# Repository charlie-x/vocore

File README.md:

# vocore eagle BRD files

Eagle BRD files for the VoCore and the VoCore dock, 7.x Eagle

notes:

	VIAs and drill sizes/restring need to be set for your board house.
	I'm using a temporary 4 layer DRC
	Layers are setup so shouldn't be any blind/buried vias

NOT BUILD TESTED - THERE WILL BE ERRORS!

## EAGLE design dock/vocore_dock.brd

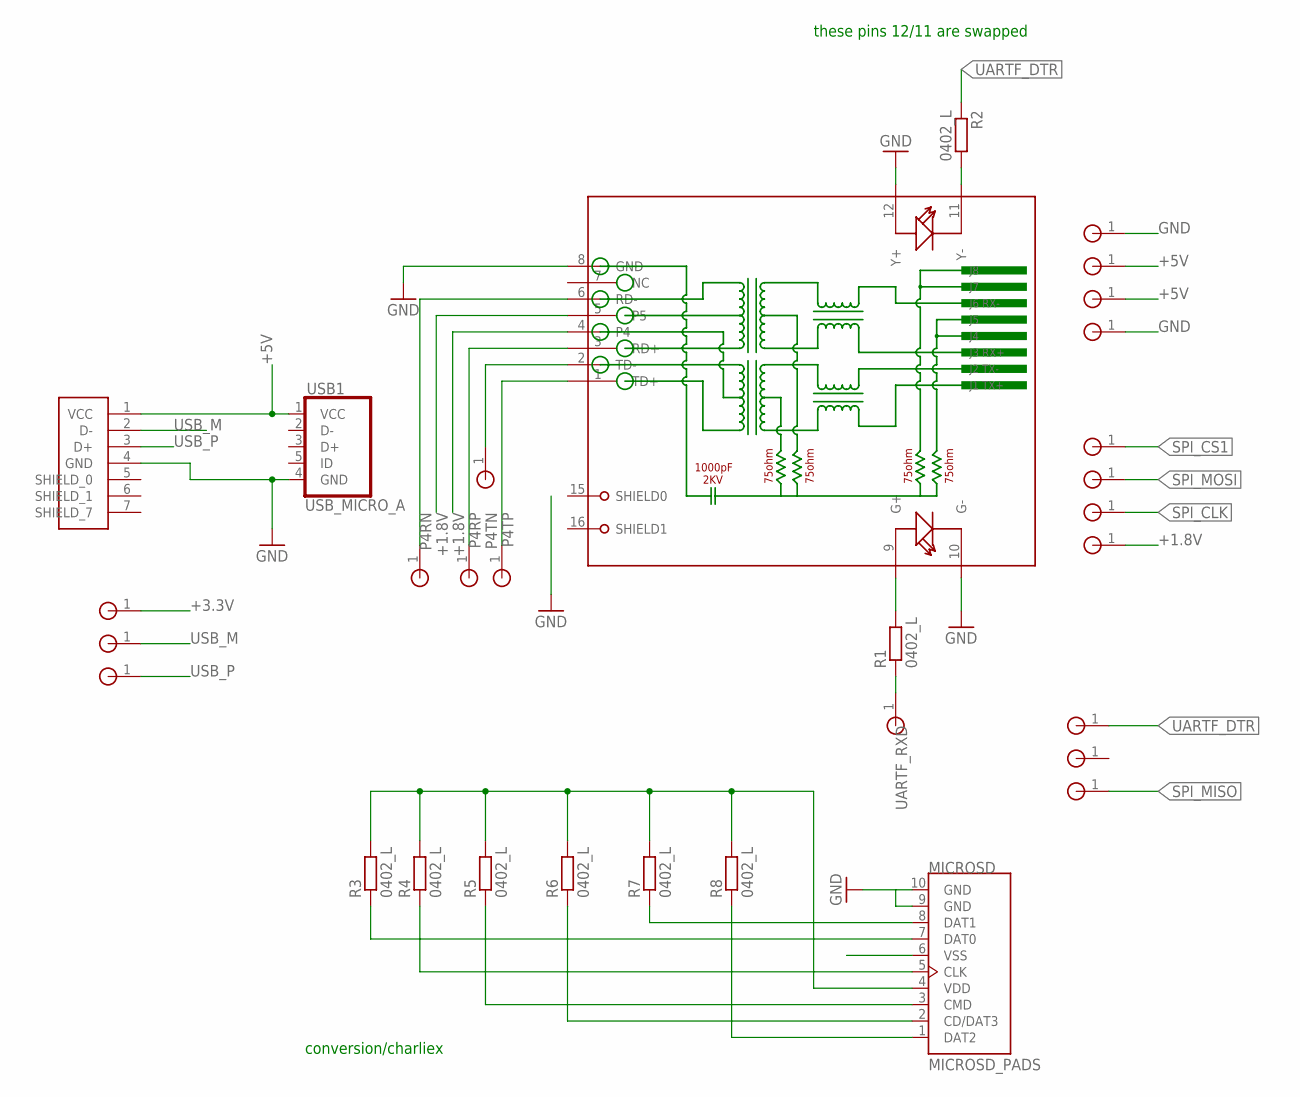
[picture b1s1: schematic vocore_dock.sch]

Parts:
MICROSD: MICROSD_PADS; MICROSD_PADS_1PRIMARY
PB04, PB05, PB06, PB07, PB12, PB13, PB14, PB15, PB16, PB17, PB18: PORT_1PIN; PORT_1PIN_DECAL_1PRIMARY
PL05, PL06, PL07, PL08: PORT_1PIN; PORT_1PIN_DECAL_1PRIMARY
PT01, PT02, PT03, PT04: PORT_1PIN; PORT_1PIN_DECAL_1PRIMARY
R1, R2, R3, R4, R5, R6, R7, R8: 0402_L; 0402_L_1PRIMARY
RJ45: RJ45ALED; RJ45ALED_1PRIMARY
USB1: USB_MICRO_A; USB_MICRO_A_1PRIMARY
USB2: USB_FULL_TALL; USB_FULL_TALL_1PRIMARY

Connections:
+1.8V: PL05.1, RJ45.4, RJ45.5
+3.3V: MICROSD.4 (VDD), PB18.1, R3.2, R4.2, R5.2, R6.2, R7.2, R8.2
+5V: PT02.1, PT03.1, USB1.1 (VCC), USB2.1 (VCC)
GND: MICROSD.6 (VSS), MICROSD.9 (GND), MICROSD.10 (GND), PT01.1, PT04.1, RJ45.8 (GND), RJ45.10 (G-), RJ45.12 (Y+), USB1.4 (GND), USB2.4 (GND)
LED_G: R1.2, RJ45.9 (G+)
LED_Y: R2.2, RJ45.11 (Y-)
P4RN: PB15.1, RJ45.6 (RD-)
P4RP: PB14.1, RJ45.3 (RD+)
P4TN: PB12.1, RJ45.2 (TD-)
P4TP: PB13.1, RJ45.1 (TD+)
SPI_CLK: MICROSD.5 (CLK), PL06.1, R4.1
SPI_CS1: MICROSD.2 (CD/DAT3), PL08.1, R6.1
SPI_MISO: MICROSD.7 (DAT0), PB05.1, R3.1
SPI_MOSI: MICROSD.3 (CMD), PL07.1, R5.1
SPI_RSV1: MICROSD.8 (DAT1), R7.1
SPI_RSV2: MICROSD.1 (DAT2), R8.1
UARTF_DTR: PB07.1, R2.1
UARTF_RXD: PB04.1, R1.1
USB_M: PB16.1, USB2.2 (D-)
USB_P: PB17.1, USB2.3 (D+)

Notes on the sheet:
these pins 12/11 are swapped
conversion/charliex

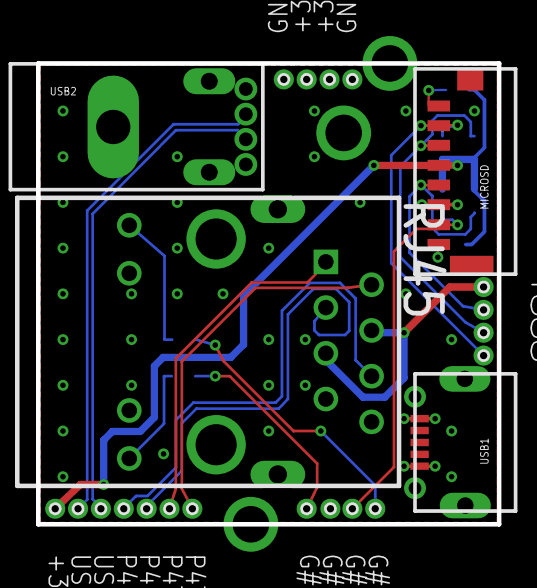
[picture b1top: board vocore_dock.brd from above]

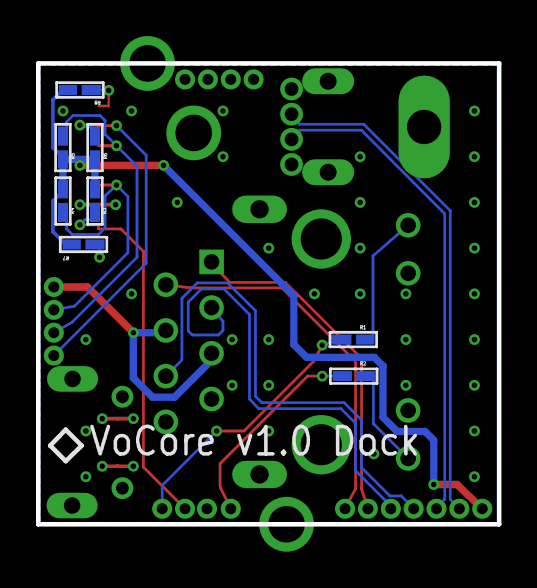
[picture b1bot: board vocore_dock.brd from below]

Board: 4 copper layers, 25.6 x 25.6 mm, 34 parts (8 on the bottom side), 20 nets.

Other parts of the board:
HOLE1, HOLE2, HOLE3: HOLE_80MIL; HOLE_80MIL_1PRIMARY

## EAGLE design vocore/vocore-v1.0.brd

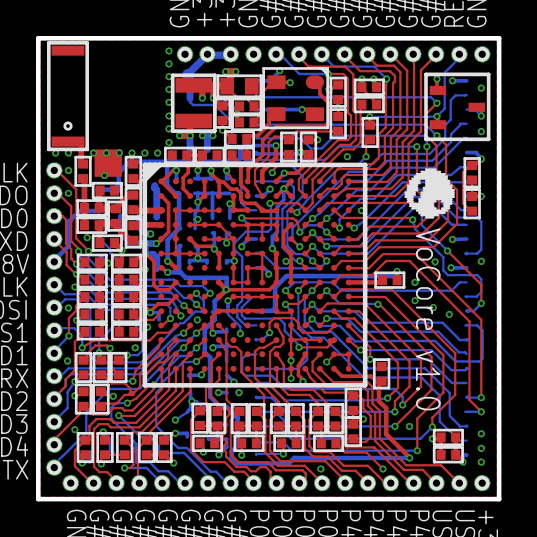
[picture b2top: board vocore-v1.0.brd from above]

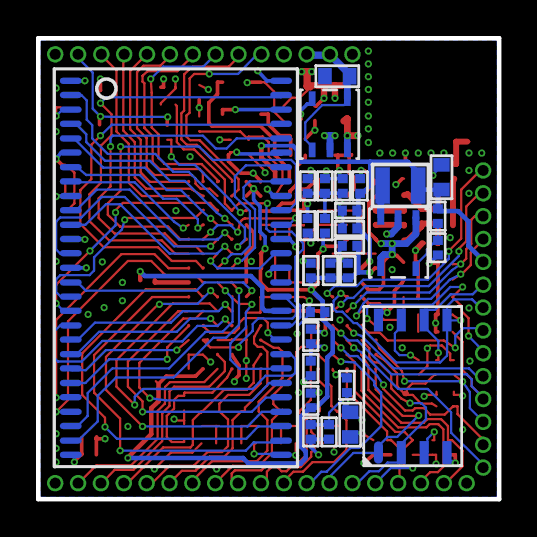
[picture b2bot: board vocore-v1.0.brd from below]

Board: 4 copper layers, 25.6 x 25.6 mm, 146 parts (29 on the bottom side), 113 nets.

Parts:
C2, C4, C6, C7, C8, C9, C10, C14, C15, C16, C17, C18, C35, C36, C37, C38, C40, C42, C43, C48, C50, C77, C79, C84, C92, C93, C98, C104, C108, C109, C110, C111, C112, C113, C114, C161, C251, C279, C387, C388, C389, C390, C391, C414, C422, C443: 0402; 0402_1PRIMARY
C103, C105, C106, C107: 0603; 0603_1PRIMARY
CON2: 5020; 5020_1PRIMARY
D1: 0402; 0402_1PRIMARY
L11, L12: 0402; 0402_1PRIMARY
L14, L15: 0806; 0806_1PRIMARY
PB00, PB01, PB02, PB03, PB04, PB05, PB06, PB07, PB08, PB09, PB10, PB11, PB12, PB13, PB14, PB15, PB16, PB17, PB18: PORT_1PIN_DECAL; PORT_1PIN_DECAL_1PRIMARY
PL01, PL02, PL03, PL04, PL05, PL06, PL07, PL08, PL09, PL10, PL11, PL12, PL13, PL14: PORT_1PIN_DECAL; PORT_1PIN_DECAL_1PRIMARY
PT01, PT02, PT03, PT04, PT05, PT06, PT07, PT08, PT09, PT10, PT11, PT12, PT13, PT14: PORT_1PIN_DECAL; PORT_1PIN_DECAL_1PRIMARY
R1, R8, R26, R27, R28, R29, R50, R55, R56, R57, R58, R67, R68, R69, R70, R71, R94, R95, R107, R118, R119, R142, R144, R150, R154, R189, R192, R193, R212, R293, R300, R308, R318: 0402; 0402_1PRIMARY
SR1, SR2: 0402; 0402_1PRIMARY
TEST1: TEST_POINT_GND; TEST_POINT_GND_1PRIMARY
U1: TFBGA196; TFBGA196_1PRIMARY
U3: SO8; SO8_1PRIMARY
U8, U9: LDO1; LDO1_1PRIMARY
U25: U4; U4_1PRIMARY
U33: Y1; Y1_1PRIMARY
U35: TSOP2-54P-400MIL; TSOP2-54P-400MIL_1PRIMARY

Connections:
1V8_FB: R67.1, R68.2, U8.5
1V8_SW: L14.1, U8.3
3V3_FB: R69.2, R70.1, U9.5
3V3_SW: L15.1, U9.3
$$$22498: U1.7, U33.1
$$$22629: C15.2, R212.1, U33.3
+1.2V: C16.1, C93.1, C98.1, C104.1, C109.1, C110.1, C111.1, U1.10, U1.23, U1.24, U1.79, U1.85, U1.93, U1.103, U1.107, U1.117, U1.195
+1.8V: C2.1, C106.1, C108.1, C161.1, L14.2, PL05.1, R68.1, U1.8, U1.86
+3.3V: C9.1, C17.1, C42.1, C84.1, C92.1, C105.2, C107.1, C112.1, C113.1, C114.1, C251.2, C387.1, C388.1, C389.1, C390.1, C391.1, C414.1, C422.1, C443.2, L15.2, PB18.1, R69.1, R71.1, R144.1, R192.2, R293.1, SR2.1, U1.9, U1.15, U1.52, U1.57, U1.59, U1.75, U1.80, U1.89, U1.94, U1.100, U1.108, U1.114, U1.131, U1.132, U1.133, U1.134, U1.179, U3.8, U8.1, U8.4, U25.3, U35.1, U35.3, U35.9, U35.14, U35.27, U35.43, U35.49
+5V: C103.1, PT02.1, PT03.1, U9.1, U9.4
EPHY0R_RC: C48.1, R26.2, R28.2
EPHY0T_RC: C50.1, R27.2, R29.2
EPHY4R_RC: C79.1, R56.2, R58.2
EPHY4T_RC: C77.1, R55.2, R57.2
EPHY_RES: R50.2, U1.186
GND: C2.2, C4.2, C6.2, C7.2, C8.2, C9.2, C10.1, C14.1, C15.1, C16.2, C17.2, C18.1, C40.2, C42.2, C43.2, C48.2, C50.2, C77.2, C79.2, C84.2, C92.2, C93.2, C98.2, C103.2, C104.2, C105.1, C106.2, C107.2, C108.2, C109.2, C110.2, C111.2, C112.2, C113.2, C114.2, C161.2, C251.1, C387.2, C388.2, C389.2, C390.2, C391.2, C414.2, C422.2, C443.1, D1.2, L11.2, PB00.1, PT01.1, PT04.1, PT14.1, R1.2, R8.1, R50.1, R67.2, R70.2, R94.2, R95.2, R107.2, R118.1, R119.2, R142.1, R150.1, R154.2, R308.2, R318.2, TEST1.1, U1.1, U1.4, U1.16, U1.18, U1.30, U1.31, U1.32, U1.33, U1.44, U1.45, U1.46, U1.47, U1.48, U1.49, U1.50, U1.51, U1.58, U1.60, U1.61, U1.62, U1.63, U1.64, U1.65, U1.71, U1.72, U1.73, U1.74, U1.76, U1.77, U1.78, U1.90, U1.91, U1.92, U1.104, U1.105, U1.106, U1.118, U1.119, U1.120, U1.121, U1.135, U1.136, U1.150, U1.164, U1.165, U1.166, U1.178, U1.181, U1.182, U1.192, U1.196, U3.4, U8.2, U9.2, U25.2, U33.2, U33.4, U35.6, U35.12, U35.28, U35.41, U35.46, U35.52, U35.54
GPIO0: PT09.1, U1.26
I2C_CLK: PT12.1, U1.28
I2C_SD: PT11.1, U1.27
JTAG_CLK: PT07.1, U1.12
JTAG_RST: PT06.1, U1.11
JTAG_TDI: PT10.1, U1.14
JTAG_TDO: PT05.1, U1.25
JTAG_TMS: PT08.1, U1.13
LED0: PL03.1, R308.1, U1.129
LED1: PL09.1, R154.1, U1.141
LED2: PL11.1, R150.2, U1.144
LED3: PL12.1, R144.2, U1.155
LED4: PL13.1, R118.2, U1.158
LED_WLAN: R142.2, R193.2, U1.127
LED_WLAN+: D1.1, R193.1
P0RN: PB11.1, R26.1, U1.145
P0RP: PB10.1, R28.1, U1.159
P0TN: PB08.1, R27.1, U1.173
P0TP: PB09.1, R29.1, U1.187
P4RN: PB15.1, R56.1, U1.177
P4RP: PB14.1, R58.1, U1.191
P4TN: PB12.1, R55.1, U1.163
P4TP: PB13.1, R57.1, U1.149
RESET: PT13.1, R189.2, U25.1
RESET_PORST: R189.1, U1.38
SDRAM_A0: U1.98, U35.23
SDRAM_A1: U1.111, U35.24
SDRAM_A2: U1.110, U35.25
SDRAM_A3: U1.109, U35.26
SDRAM_A4: U1.126, U35.29
SDRAM_A5: U1.125, U35.30
SDRAM_A6: U1.124, U35.31
SDRAM_A7: U1.140, U35.32
SDRAM_A8: U1.139, U35.33
SDRAM_A9: U1.123, U35.34
SDRAM_A10: U1.154, U35.22
SDRAM_A11: U1.138, U35.35
SDRAM_A12: U1.153, U35.36
SDRAM_BA0: U1.152, U35.20
SDRAM_BA1: U1.168, U35.21
SDRAM_CAS: U1.40, U35.17
SDRAM_CKE: R293.2, U1.39, U35.37
SDRAM_CLK: R300.2, U35.38
SDRAM_CS: U1.137, U35.19
SDRAM_D0: U1.66, U35.2
SDRAM_D1: U1.53, U35.4
SDRAM_D2: U1.54, U35.5
SDRAM_D3: U1.55, U35.7
SDRAM_D4: U1.56, U35.8
SDRAM_D5: U1.67, U35.10
SDRAM_D6: U1.81, U35.11
SDRAM_D7: U1.68, U35.13
SDRAM_D8: U1.82, U35.42
SDRAM_D9: U1.69, U35.44
SDRAM_D10: U1.70, U35.45
SDRAM_D11: U1.95, U35.47
SDRAM_D12: U1.96, U35.48
SDRAM_D13: U1.83, U35.50
SDRAM_D14: U1.97, U35.51
SDRAM_D15: U1.84, U35.53
SDRAM_DQML: U1.122, U35.15
SDRAM_DQMU: U1.167, U35.39
SDRAM_R51: R300.1, U1.112
SDRAM_RAS: U1.151, U35.18
SDRAM_WE: U1.41, U35.16
SPI_CLK: PL06.1, SR1.2, U3.6
SPI_CLK_L: R94.1, SR1.1, U1.169
SPI_CS0: PB06.1, U1.183, U3.1
SPI_CS1: PL08.1, U1.142
SPI_HOLD: R71.2, U3.7
SPI_MISO: PB05.1, U1.156, U3.2
SPI_MOSI: PL07.1, R95.1, U1.115, U3.5
SPI_WE: SR2.2, U3.3
UARTF_CTS: PL02.1, U1.130
UARTF_DCD: PL01.1, U1.116
UARTF_DSR: PL10.1, U1.143
UARTF_DTR: PB07.1, U1.172
UARTF_RIN: PL14.1, U1.157
UARTF_RTS: PB02.1, U1.184
UARTF_RXD: PB03.1, R192.1, U1.171
UARTF_TXD: PL04.1, R119.1, U1.128
UARTL_RXD2: PB04.1, R318.1, U1.185
UARTL_TXD2: PB01.1, R107.1, U1.170
UPHY_RES: C43.1, R8.2, U1.193
USB_M: PB16.1, U1.180
USB_P: PB17.1, U1.194
WL_ANT: C36.2, C279.1, L12.2
WL_ANT_C: C279.2, CON2.2
WL_RF0_OUTL: C35.2, C36.1, C37.1, L11.1
WL_RF0_OUTN: C38.1, U1.43
WL_RF0_OUTP: C35.1, U1.29
WL_RF0_OUTR: C37.2, C38.2, C40.1, L12.1
WL_V12_CAP: C4.1, C6.1, C7.1, C8.1, U1.5, U1.17, U1.19, U1.36, U1.37
WL_V12_PLL: C14.2, U1.20, U1.34, U1.35
WL_V12_RES: C10.2, R1.1, U1.22
WL_V33: C18.2, U1.6
WL_X2: R212.2, U1.21

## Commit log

2015-02-07 added brd's
    NOT TESTED!
2015-02-07 text update
2015-02-07 added 4 layer rules.
2015-02-07 added 4 layer rules
2015-02-07 fixed air wires.
2015-02-07 added lbr
2015-02-07 flipped layer 1 and 16
2015-02-07 adding lbr.
2015-02-08 via's restringed.
2015-02-08 drc settings changed, restring 2mil
2015-02-08 created schematic schematic/brd are in sync. gnd's are missing. some holes wrong size. DRC is wrong restrings?
2015-02-08 flipped 16 and 1 again.. it was right the first time :)
2015-02-09 removed a bad trace when i was fixing short airwires.
2015-02-09 adding gnd's
2015-03-01 fixed top/bottom

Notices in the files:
dock/vocore_dock.brd:
copyright © 2014 vonger.cn
vocore/vocore-v1.0.brd:
copyright © 2014 vonger.net
